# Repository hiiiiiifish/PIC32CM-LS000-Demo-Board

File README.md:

# PIC32CM-LS000-Demo-Board

Yes a very professional demo board, please do NOT try and learn from this projekt
thank you

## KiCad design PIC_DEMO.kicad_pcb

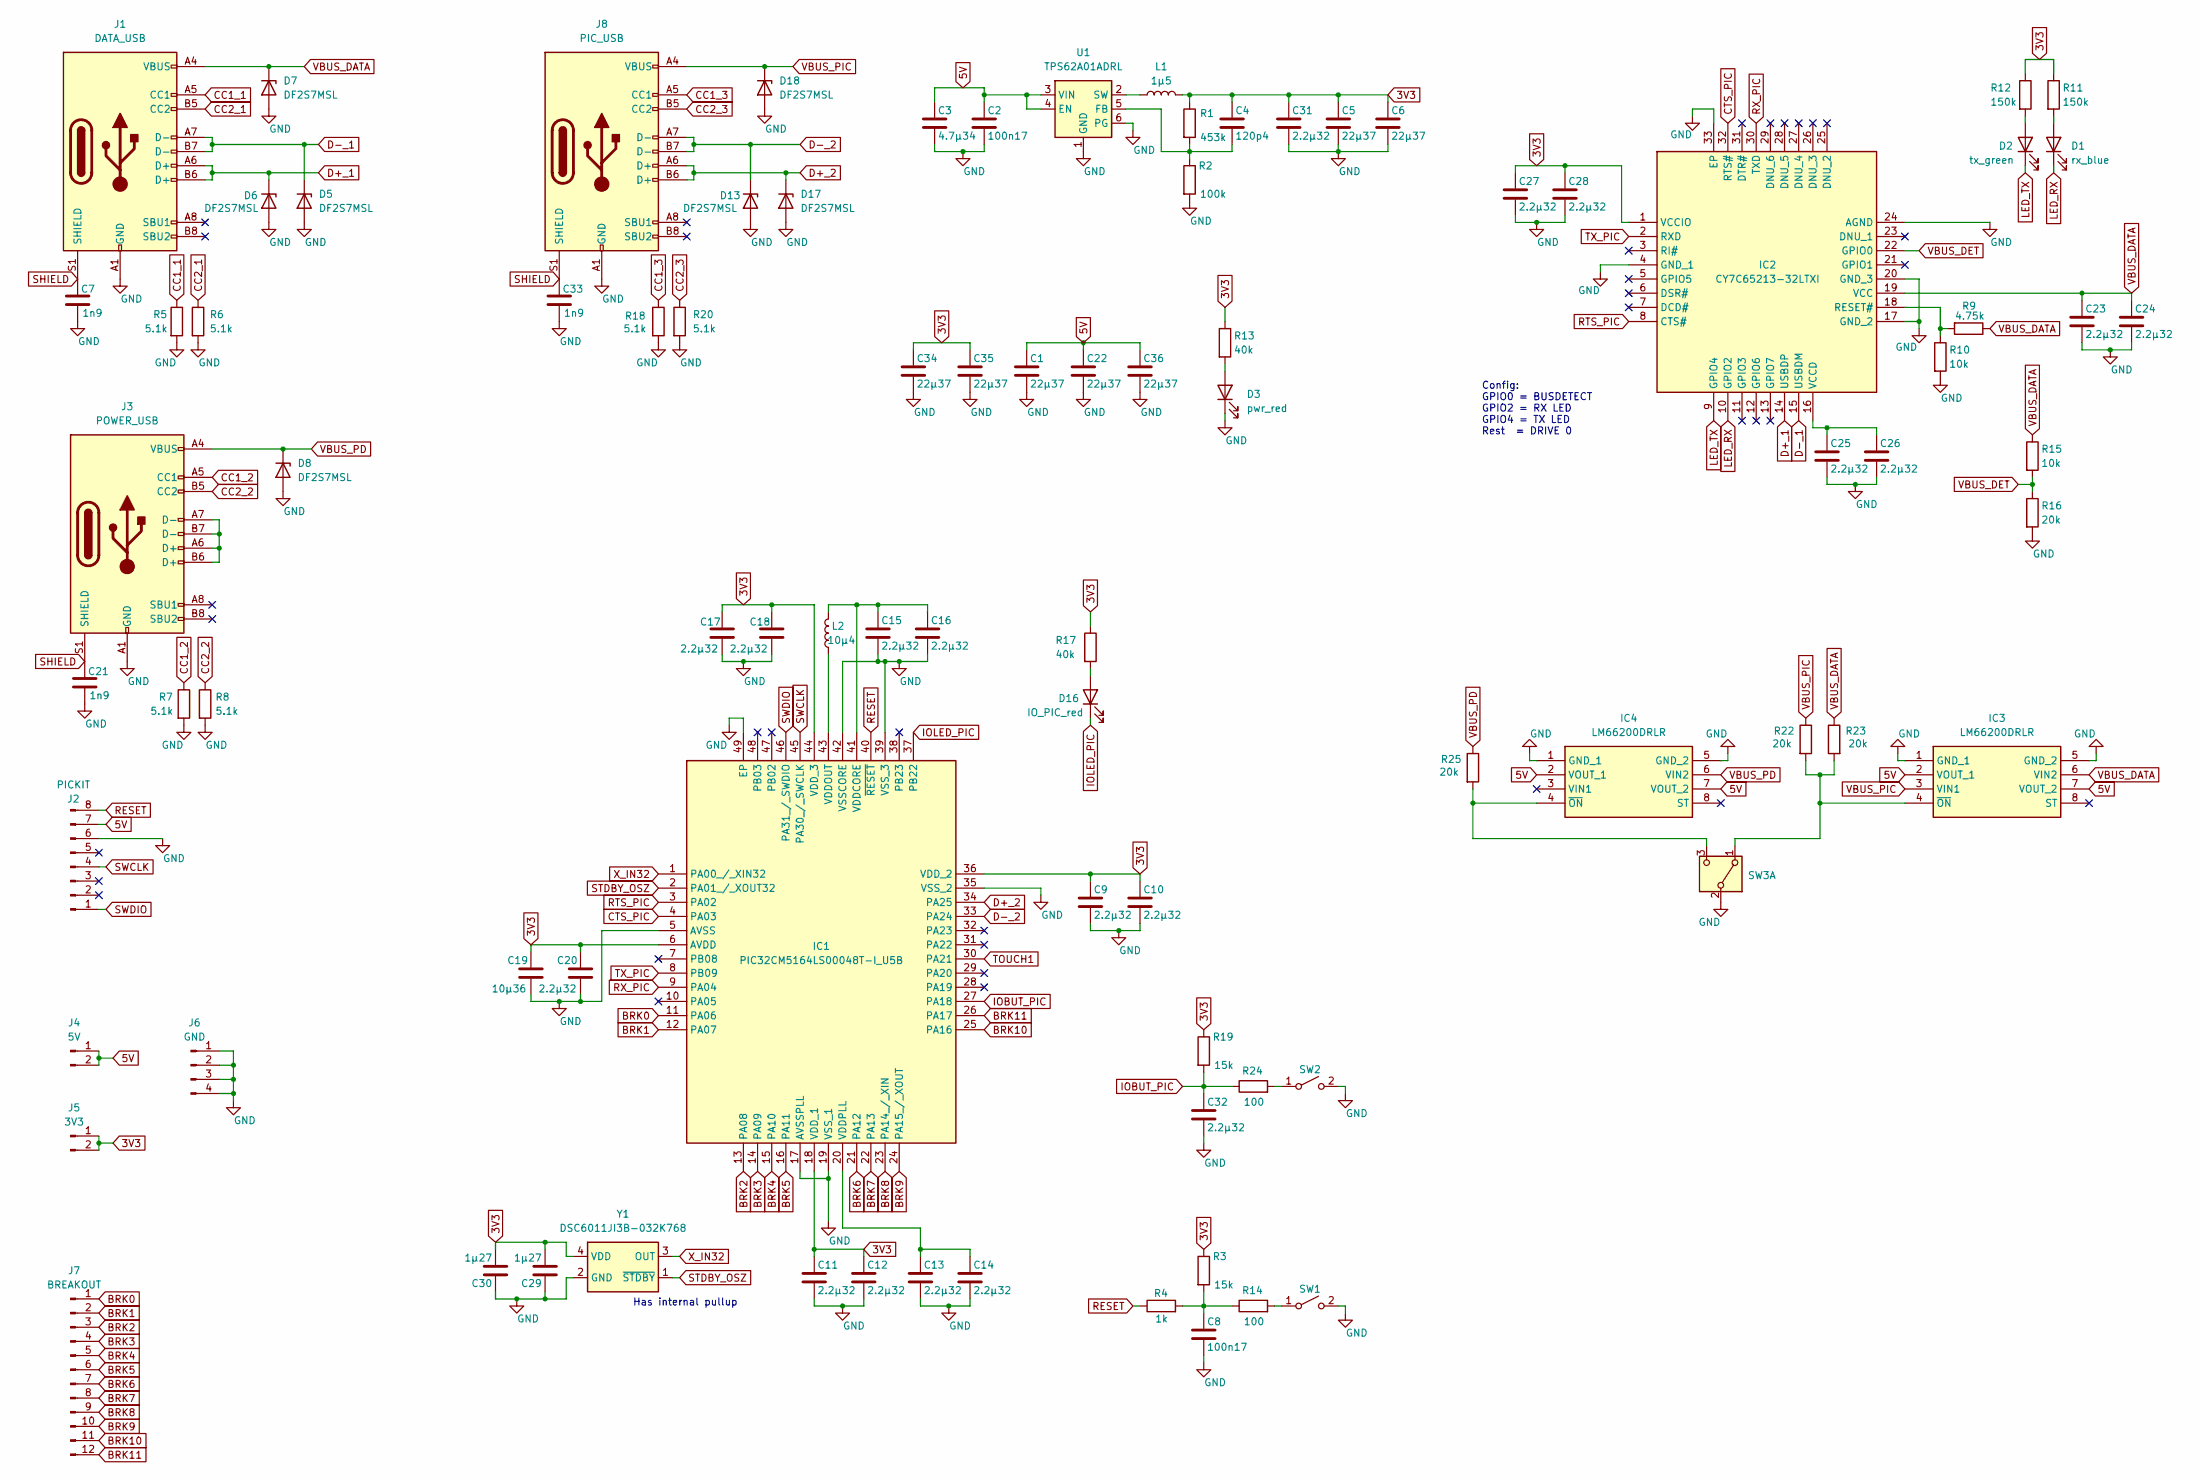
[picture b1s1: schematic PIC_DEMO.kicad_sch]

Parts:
C1, C5, C6, C22, C34, C35, C36: 22µ37; C_0603_1608Metric
C2, C8: 100n17; C_0402_1005Metric
C3: 4.7µ34; C_0603_1608Metric
C4: 120p4; C_0603_1608Metric
C7, C21, C33: 1n9; C_0603_1608Metric
C9, C10, C11, C12, C13, C14, C15, C16, C17, C18, C20, C23, C24, C25, C26, C27, C28, C31, C32: 2.2µ32; C_0402_1005Metric
C19: 10µ36; C_0603_1608Metric
C29, C30: 1µ27; C_0402_1005Metric
D1: rx_blue; LED_0603_1608Metric
D2: tx_green; LED_0603_1608Metric
D3: pwr_red; LED_0603_1608Metric
D5, D6, D7, D8, D13, D17, D18: DF2S7MSL; DF2S7MSLL3F
D16: IO_PIC_red; LED_0603_1608Metric
IC1: PIC32CM5164LS00048T-I_U5B; QFN50P700X700X90-49N-D; Manufacturer_Part_Number PIC32CM5164LS00048T-I/U5B
IC2: CY7C65213-32LTXI; QFN50P500X500X100-33M-D; Mouser Part Number 727-CY7C65213-32LTXI
IC3, IC4: LM66200DRLR; SOTFL50P160X60-8N; Mouser Part Number 595-LM66200DRLR
J1: DATA_USB; USB4215-03-A
J2: PICKIT; PinHeader_1x08_P2.54mm_Horizontal
J3: POWER_USB; USB4215-03-A
J4: 5V; PinHeader_1x02_P2.54mm_Vertical
J5: 3V3; PinHeader_1x02_P2.54mm_Vertical
J6: GND; PinHeader_2x02_P2.54mm_Vertical
J7: BREAKOUT; PinHeader_1x12_P2.54mm_Vertical
J8: PIC_USB; USB4215-03-A
L1: 1µ5; L_0805_2012Metric
L2: 10µ4; L_0805_2012Metric
R1: 453k; R_0603_1608Metric
R2: 100k; R_0603_1608Metric
R3, R19: 15k; R_0603_1608Metric
R4: 1k; R_0603_1608Metric
R5, R6, R7, R8, R18, R20: 5.1k; R_0603_1608Metric
R9: 4.75k; R_0603_1608Metric
R10, R15: 10k; R_0603_1608Metric
R11, R12: 150k; R_0603_1608Metric
R13, R17: 40k; R_0603_1608Metric
R14, R24: 100; R_0603_1608Metric
R16, R22, R23, R25: 20k; R_0603_1608Metric
SW1, SW2: SW_SPST; TS046650BK100SMTTR
SW3: SW; SLW-105558-2A-N-D
U1: TPS62A01ADRL; SOT-563
Y1: DSC6011JI3B-032K768; DSC6011JI3B-032K768T; Manufacturer_Part_Number DSC6011JI1B-008.0000T

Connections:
3V3: C4.1, C5.1, C6.1, C9.1, C10.1, C11.1, C12.1, C17.1, C18.1, C19.1, C20.1, C27.1, C28.1, C29.2, C30.2, C31.1, C34.1, C35.1, IC1.6 (AVDD), IC1.18 (VDD_1), IC1.36 (VDD_2), IC1.44 (VDD_3), IC2.1 (VCCIO), J5.1, J5.2, L1.2, R1.1, R3.1, R11.1, R12.1, R13.1, R17.1, R19.1, Y1.4 (VDD)
5V: C1.1, C2.1, C3.1, C22.1, C36.1, IC3.2 (VOUT_1), IC3.7 (VOUT_2), IC4.2 (VOUT_1), IC4.7 (VOUT_2), J2.7, J4.1, J4.2, U1.3 (VIN), U1.4 (EN)
BRK0: IC1.11 (PA06), J7.1
BRK1: IC1.12 (PA07), J7.2
BRK2: IC1.13 (PA08), J7.3
BRK3: IC1.14 (PA09), J7.4
BRK4: IC1.15 (PA10), J7.5
BRK5: IC1.16 (PA11), J7.6
BRK6: IC1.21 (PA12), J7.7
BRK7: IC1.22 (PA13), J7.8
BRK8: IC1.23 (PA14_/_XIN), J7.9
BRK9: IC1.24 (PA15_/_XOUT), J7.10
BRK10: IC1.25 (PA16), J7.11
BRK11: IC1.26 (PA17), J7.12
CC1_1: J1.A5 (CC1), R5.1
CC1_2: J3.A5 (CC1), R7.1
CC1_3: J8.A5 (CC1), R18.1
CC2_1: J1.B5 (CC2), R6.1
CC2_2: J3.B5 (CC2), R8.1
CC2_3: J8.B5 (CC2), R20.1
CTS_PIC: IC1.4 (PA03), IC2.32 (RTS#)
D+_1: D6.1 (K), IC2.14 (USBDP), J1.A6 (D+), J1.B6 (D+)
D+_2: D17.1 (K), IC1.34 (PA25), J8.A6 (D+), J8.B6 (D+)
D-_1: D5.1 (K), IC2.15 (USBDM), J1.A7 (D-), J1.B7 (D-)
D-_2: D13.1 (K), IC1.33 (PA24), J8.A7 (D-), J8.B7 (D-)
GND: C1.2, C2.2, C3.2, C5.2, C6.2, C7.2, C8.2, C9.2, C10.2, C11.2, C12.2, C13.2, C14.2, C15.2, C16.2, C17.2, C18.2, C19.2, C20.2, C21.2, C22.2, C23.2, C24.2, C25.2, C26.2, C27.2, C28.2, C29.1, C30.1, C31.2, C32.2, C33.2, C34.2, C35.2, C36.2, D3.1 (K), D5.2 (A), D6.2 (A), D7.2 (A), D8.2 (A), D13.2 (A), D17.2 (A), D18.2 (A), IC1.5 (AVSS), IC1.17 (AVSSPLL), IC1.19 (VSS_1), IC1.35 (VSS_2), IC1.39 (VSS_3), IC1.42 (VSSCORE), IC1.49 (EP), IC2.4 (GND_1), IC2.17 (GND_2), IC2.20 (GND_3), IC2.24 (AGND), IC2.33 (EP), IC3.1 (GND_1), IC3.5 (GND_2), IC4.1 (GND_1), IC4.5 (GND_2), J1.A1 (GND), J1.B1 (GND), J2.6, J3.A1 (GND), J3.B1 (GND), J6.1, J6.2, J6.3, J6.4, J8.A1 (GND), J8.B1 (GND), R2.2, R5.2, R6.2, R7.2, R8.2, R10.2, R16.2, R18.2, R20.2, SW1.2 (B), SW2.2 (B), SW3.2 (B), U1.1 (GND), U1.6 (PG), Y1.2 (GND)
IOBUT_PIC: C32.1, IC1.27 (PA18), R19.2, R24.1
IOLED_PIC: D16.1 (K), IC1.37 (PB22)
LED_RX: D1.1 (K), IC2.10 (GPIO2)
LED_TX: D2.1 (K), IC2.9 (GPIO4)
unnamed: C8.1, R3.2, R4.2, R14.1
unnamed: D1.2 (A), R11.2
unnamed: D2.2 (A), R12.2
unnamed: D3.2 (A), R13.2
unnamed: D16.2 (A), R17.2
unnamed: C15.1, C16.1, IC1.41 (VDDCORE), L2.2
unnamed: IC1.43 (VDDOUT), L2.1
unnamed: C13.1, C14.1, IC1.20 (VDDPLL)
unnamed: IC2.18 (RESET#), R9.2, R10.1
unnamed: C25.1, C26.1, IC2.16 (VCCD)
unnamed: IC3.4 (~ON), R22.2, R23.2, SW3.1 (A)
unnamed: IC4.4 (~ON), R25.2, SW3.3 (C)
unnamed: J3.A6 (D+), J3.A7 (D-), J3.B6 (D+), J3.B7 (D-)
unnamed: R14.2, SW1.1 (A)
unnamed: R24.2, SW2.1 (A)
unnamed: C4.2, R1.2, R2.1, U1.5 (FB)
unnamed: L1.1, U1.2 (SW)
RESET: IC1.40 (~RESET), J2.8, R4.1
RTS_PIC: IC1.3 (PA02), IC2.8 (CTS#)
RX_PIC: IC1.9 (PA04), IC2.30 (TXD)
SHIELD: C7.1, C21.1, C33.1, J1.S1 (SHIELD), J3.S1 (SHIELD), J8.S1 (SHIELD)
STDBY_OSZ: IC1.2 (PA01_/_XOUT32), Y1.1 (~STDBY)
SWCLK: IC1.45 (PA30_/_SWCLK), J2.4
SWDIO: IC1.46 (PA31_/_SWDIO), J2.1
TOUCH1: IC1.30 (PA21)
TX_PIC: IC1.8 (PB09), IC2.2 (RXD)
VBUS_DATA: C23.1, C24.1, D7.1 (K), IC2.19 (VCC), IC3.6 (VIN2), J1.A4 (VBUS), J1.B4 (VBUS), R9.1, R15.1, R23.1
VBUS_DET: IC2.22 (GPIO0), R15.2, R16.1
VBUS_PD: D8.1 (K), IC4.6 (VIN2), J3.A4 (VBUS), J3.B4 (VBUS), R25.1
VBUS_PIC: D18.1 (K), IC3.3 (VIN1), J8.A4 (VBUS), J8.B4 (VBUS), R22.1
X_IN32: IC1.1 (PA00_/_XIN32), Y1.3 (OUT)

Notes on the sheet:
Config: GPIO0 = BUSDETECT GPIO2 = RX LED GPIO4 = TX LED Rest = DRIVE 0
Has internal pullup

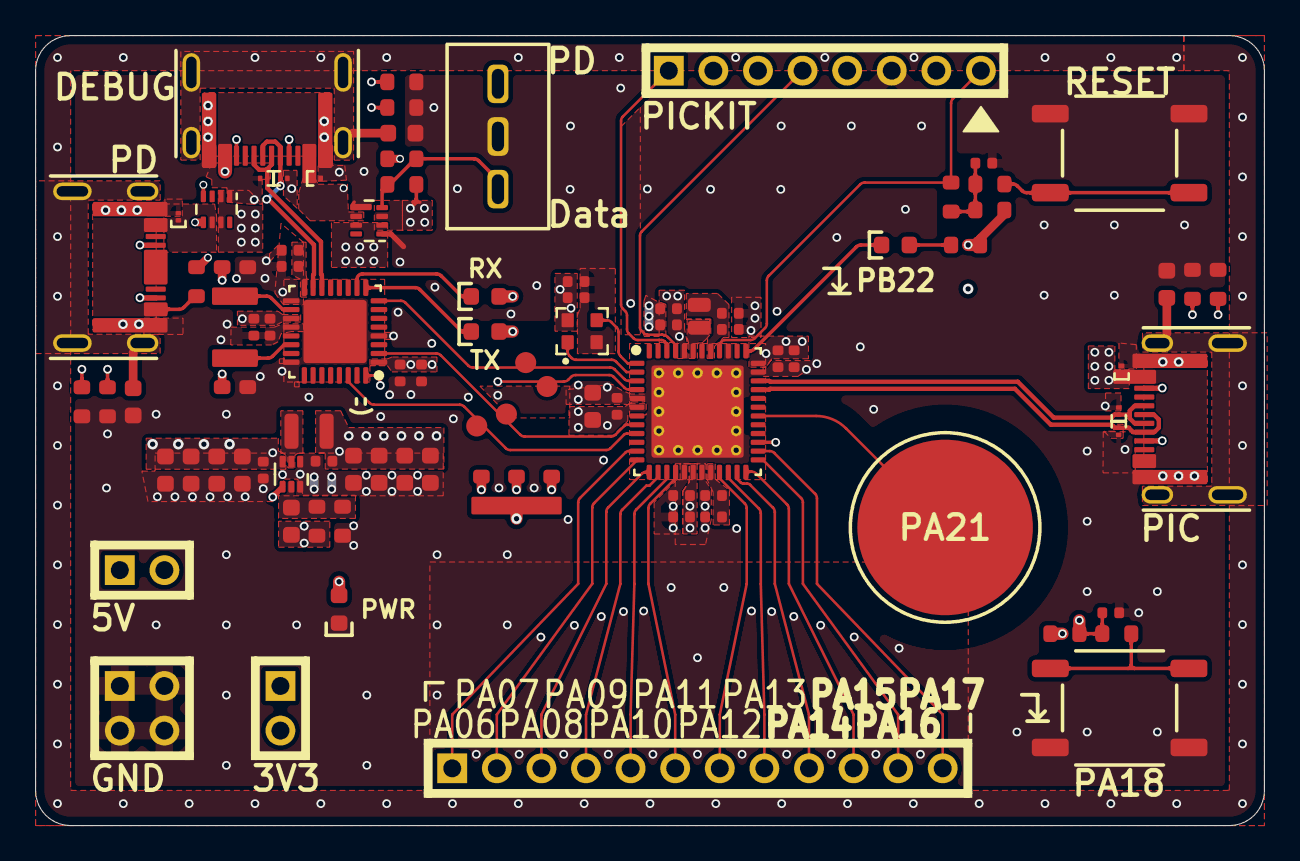
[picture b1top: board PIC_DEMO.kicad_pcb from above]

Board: 4 copper layers, 70.0 x 45.0 mm, 95 parts (0 on the bottom side), 60 nets.

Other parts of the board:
Smiley: Smile
pad_cts: (no value)
pad_rts: (no value)
pad_rx: (no value)
pad_tx: (no value)

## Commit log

2026-04-10 Yes V1 ist fertig
